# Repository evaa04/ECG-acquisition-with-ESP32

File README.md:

# ❤️ Custom ECG Acquisition System

Design of a custom electrocardiogram (ECG) acquisition system including a dedicated analog front-end PCB with galvanic isolation, ESP32-based signal acquisition, and MATLAB visualization for cardiac signal analysis.

---

## ⚡ System Architecture

The acquisition chain is structured as follows:

```text
ECG Electrodes ➔ Analog Front-End PCB ➔ ADS1115 ADC ➔ ESP32 Microcontroller ➔ MATLAB Visualization
```

The ESP32 reads the differential ECG signal from the ADS1115 and streams the data via serial communication for external visualization and processing.

---

## 🧠 Hardware Design

The system includes a custom PCB designed to acquire and condition the ECG signal.

Main hardware components:
- **INA114 & TL082:** Instrumentation amplifier and operational amplifiers used for high-common-mode rejection amplification and active analog filtering stages.
- **ISO124:** Linear isolation amplifier providing a critical galvanic isolation stage to guarantee patient safety against electrical shocks.
- **ADS1115:** High-precision 16-bit ADC used to digitize the conditioned analog ECG signal with low noise.
- **ESP32 Interface:** Microcontroller connection layer responsible for sampling the ADC data over I2C and managing high-speed serial communication.

---

## 🛠️ Assembled Hardware & Soldering Showcase

Visual inspection of the final, fully assembled and soldered printed circuit board:

| Top Layer Assembly | Bottom Layer Soldering |
| :---: | :---: |
|  |  |
| *Top view showing component placement and active ICs.* | *Bottom view showing the final solder joints and trace routing.* |

---

## 📁 Engineering Blueprints & Documentation

The native CAD design files are available directly in the root of the repository:

*   🛠️ **[View PCB Layout File (.brd)](hardware/ECG_final_project.brd)**
*   📐 **[View Schematic Diagram File (.sch)](hardware/ECG_final_project.sch)**

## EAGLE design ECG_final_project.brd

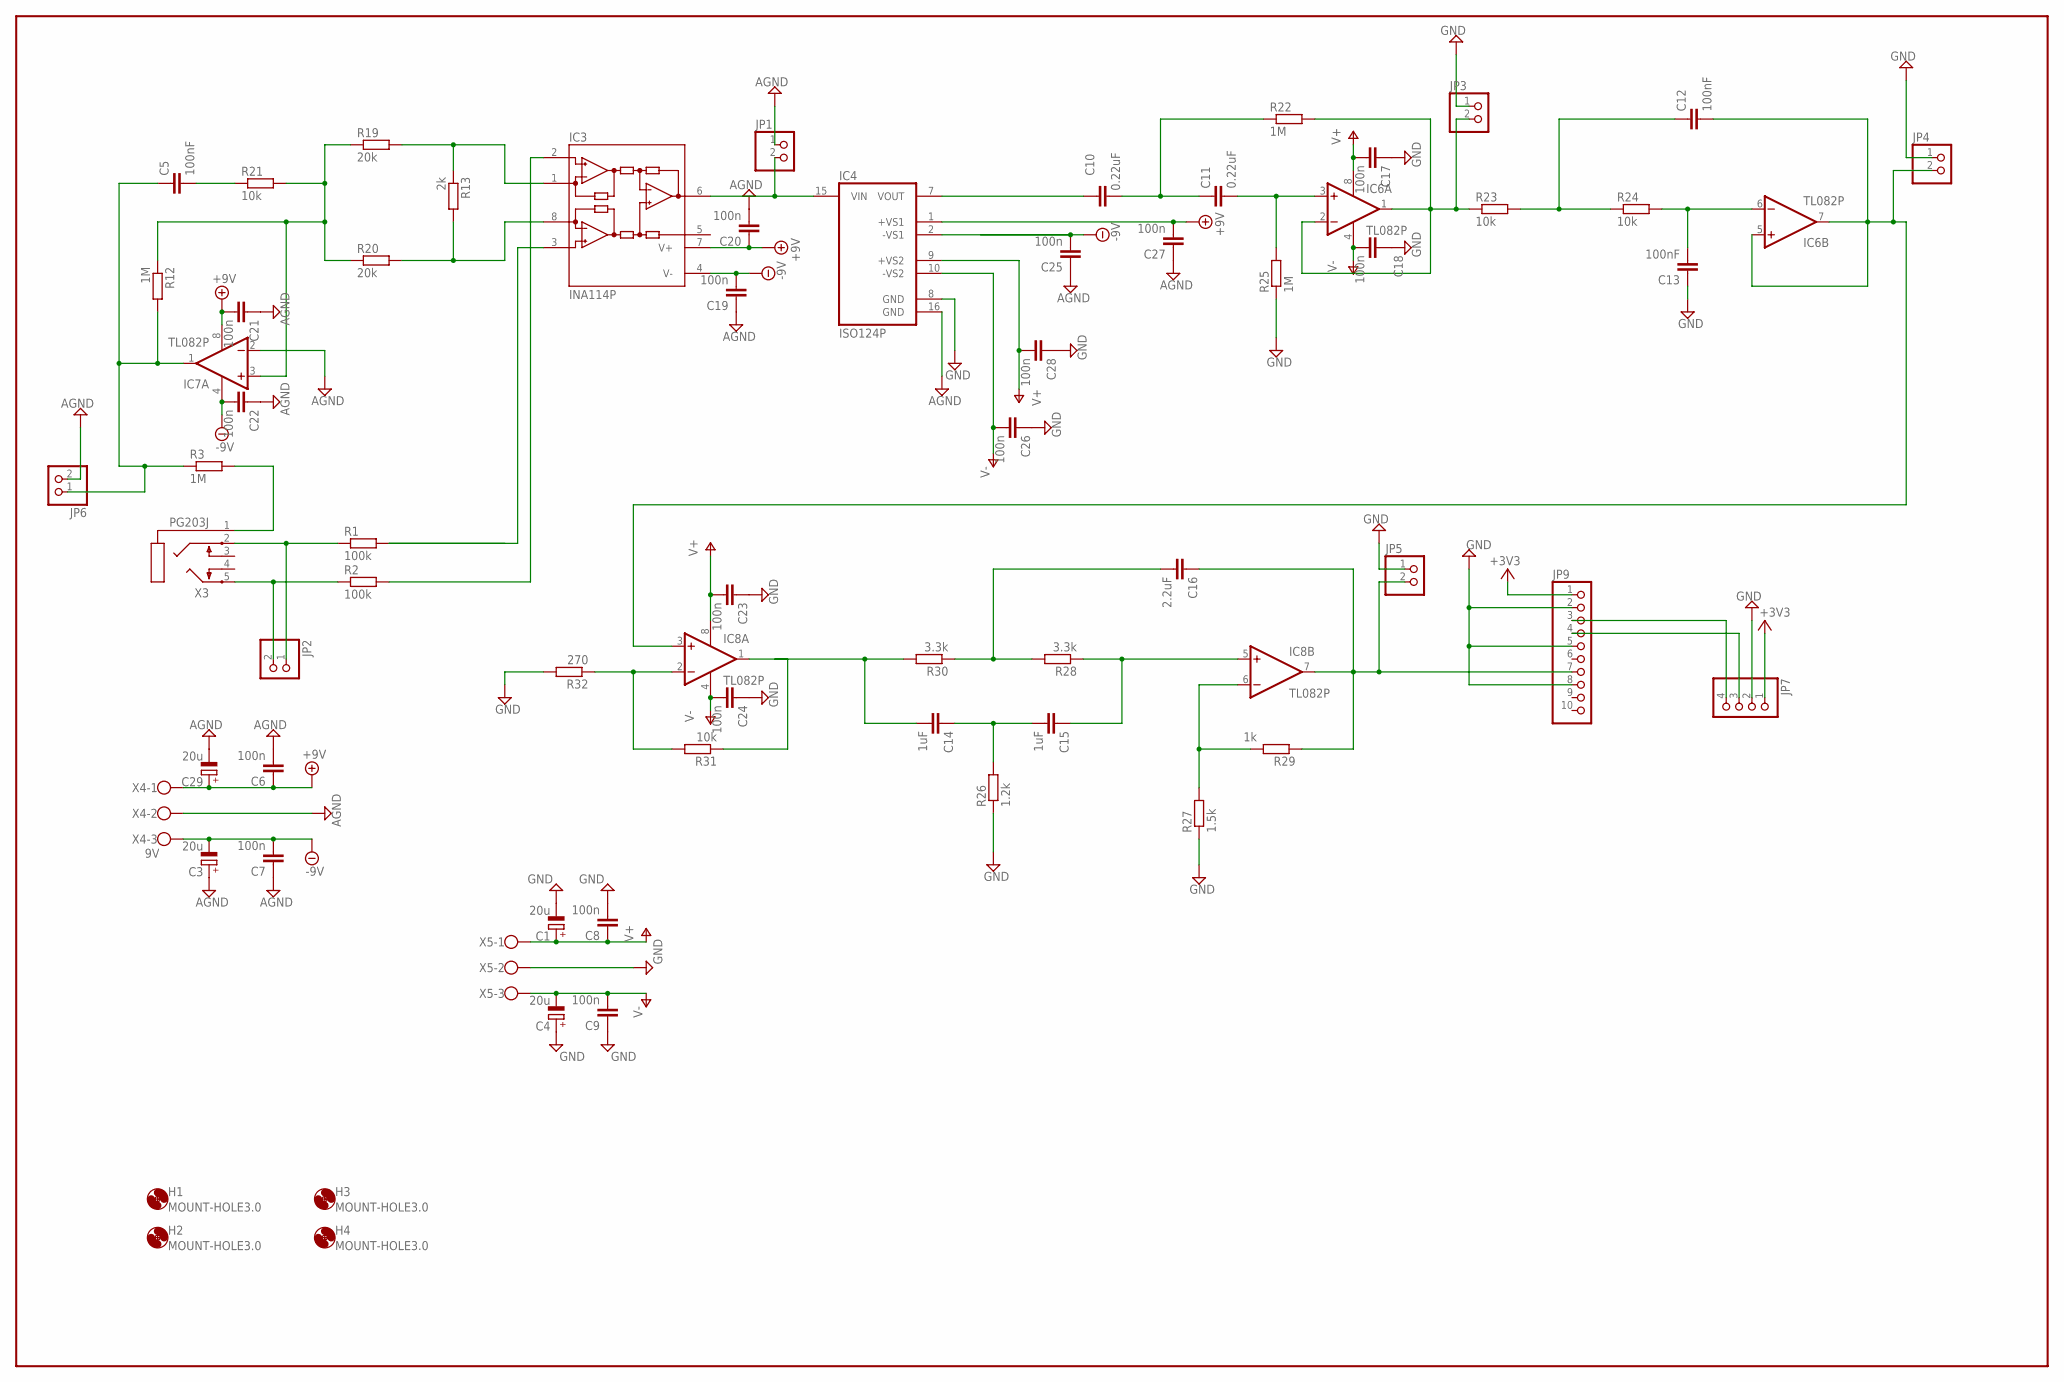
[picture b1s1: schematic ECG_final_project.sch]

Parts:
C1, C3, C4, C29: 20u; E2,5-6E
C5, C12, C13: 100nF; C025-025X050
C6, C7, C8, C9, C17, C18, C19, C20, C21, C22, C23, C24, C25, C26, C27, C28: 100n; C025-025X050
C10, C11: 0.22uF; C025-025X050
C14, C15: 1uF; C025-025X050
C16: 2.2uF; C025-025X050
H1, H2, H3, H4: MOUNT-HOLE3.0; 3,0
IC3: INA114P; DIL08
IC4: ISO124P; DIL16/8
IC6, IC7, IC8: TL082P; DIL08
JP1, JP2, JP3, JP4, JP5, JP6: PINHD-1X2; 1X02
JP7: PINHD-1X4; 1X04
JP9: PINHD-1X10; 1X10
R1, R2: 100k; 0207/10
R3, R12, R22, R25: 1M; 0207/10
R13: 2k; 0207/10
R19, R20: 20k; 0207/10
R21, R23, R24, R31: 10k; 0207/10
R26: 1.2k; 0207/10
R27: 1.5k; 0207/10
R28, R30: 3.3k; 0207/10
R29: 1k; 0207/10
R32: 270; 0207/10
X3: PG203J
X4: 9V; W237-103
X5: W237-103

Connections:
+3V3: JP7.1, JP9.1
+9V: C6.1, C20.1, C21.2, C27.2, C29.+, IC3.7 (V+), IC4.1 (+VS1), IC7.8 (V+), X4.1
-9V: C3.-, C7.2, C19.2, C22.2, C25.2, IC3.4 (V-), IC4.2 (-VS1), IC7.4 (V-), X4.3
AGND: C3.+, C6.2, C7.1, C19.1, C20.2, C21.1, C22.1, C25.1, C27.1, C29.-, IC4.16 (GND), IC7.2 (-IN), JP1.1, JP6.2, X4.2
GND: C1.-, C4.+, C8.2, C9.1, C13.1, C17.1, C18.1, C23.1, C24.1, C26.1, C28.1, IC4.8 (GND), JP3.1, JP4.1, JP5.1, JP7.2, JP9.2, JP9.5, JP9.8, R25.1, R26.1, R27.1, R32.2, X5.2
unnamed: IC7.3 (+IN), R12.1, R19.1, R20.1, R21.2
unnamed: C5.2, R21.1
unnamed: C5.1, IC7.1 (OUT), JP6.1, R3.1, R12.2
unnamed: JP7.4, JP9.3
unnamed: IC3.1 (RG), R13.1, R19.2
unnamed: IC3.8 (RG), R13.2, R20.2
unnamed: IC3.6 (OUT), IC4.15 (VIN), JP1.2
unnamed: C10.1, IC4.7 (VOUT)
unnamed: C10.2, C11.1, R22.1
unnamed: C11.2, IC6.3 (+IN), R25.2
unnamed: JP7.3, JP9.4
unnamed: IC6.1 (OUT), IC6.2 (-IN), JP3.2, R22.2, R23.1
unnamed: C12.1, R23.2, R24.1
unnamed: C13.2, IC6.6 (-IN), R24.2
unnamed: C12.2, IC6.5 (+IN), IC6.7 (OUT), IC8.3 (+IN), JP4.2
unnamed: R3.2, X3.1
unnamed: IC8.2 (-IN), R31.2, R32.1
unnamed: IC8.1 (OUT), R31.1
unnamed: C16.2, R28.2, R30.1
unnamed: C16.1, IC8.7 (OUT), JP5.2, JP9.7, R29.1
unnamed: IC8.6 (-IN), R27.2, R29.2
unnamed: C14.2, R30.2
unnamed: C14.1, C15.2, R26.2
unnamed: C15.1, IC8.5 (+IN), R28.1
unnamed: IC3.2 (-IN), R2.2
unnamed: IC3.3 (+IN), R1.2
unnamed: JP2.1, R1.1, X3.2
unnamed: JP2.2, R2.1, X3.5
V+: C1.+, C8.1, C17.2, C23.2, C28.2, IC4.9 (+VS2), IC6.8 (V+), IC8.8 (V+), X5.1
V-: C4.-, C9.2, C18.2, C24.2, C26.2, IC4.10 (-VS2), IC6.4 (V-), IC8.4 (V-), X5.3

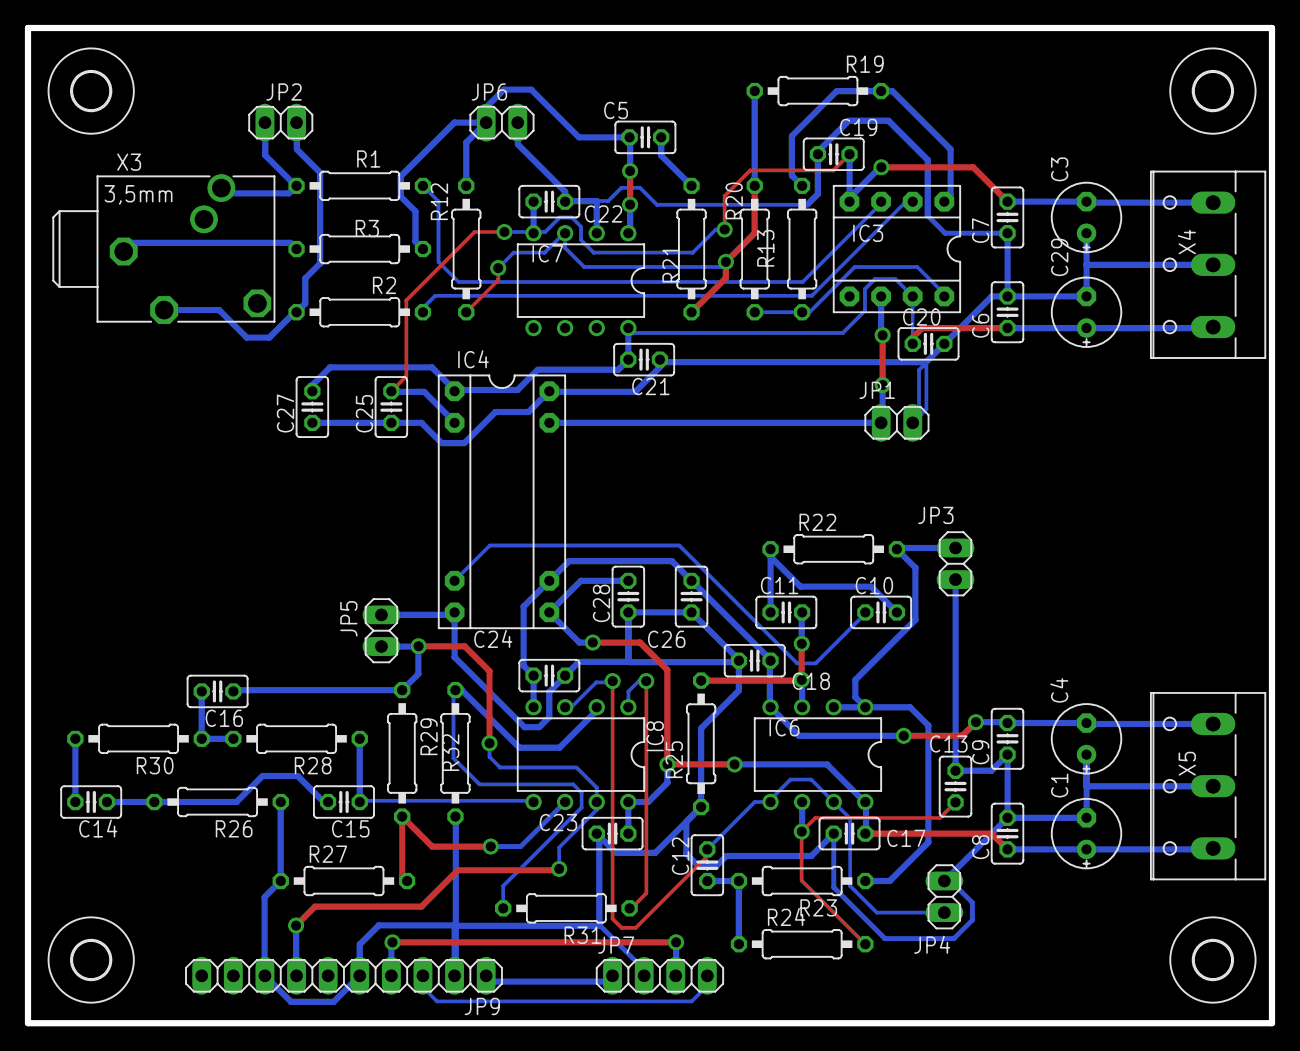
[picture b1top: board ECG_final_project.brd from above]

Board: 2 copper layers, 100.0 x 80.0 mm, 67 parts (0 on the bottom side), 35 nets.

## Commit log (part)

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2026-03-11 Revise README for custom ECG acquisition system
    Updated the README to provide a detailed overview of the custom ECG acquisition system, including project objectives, system architecture, hardware design, and firmware details.
2026-03-11 Add initial content to figures file
2026-03-11 Create figures
2026-03-11 Fix image paths in README.md
    Updated image paths in README to reflect new directory structure.
2026-03-11 Add new file code with a single character 'a'
2026-03-11 Revise README with updated project details
    Updated project description and hardware components list. Removed firmware section and example code.
2026-03-11 Remove project overview from README
    Removed project overview section from README.
